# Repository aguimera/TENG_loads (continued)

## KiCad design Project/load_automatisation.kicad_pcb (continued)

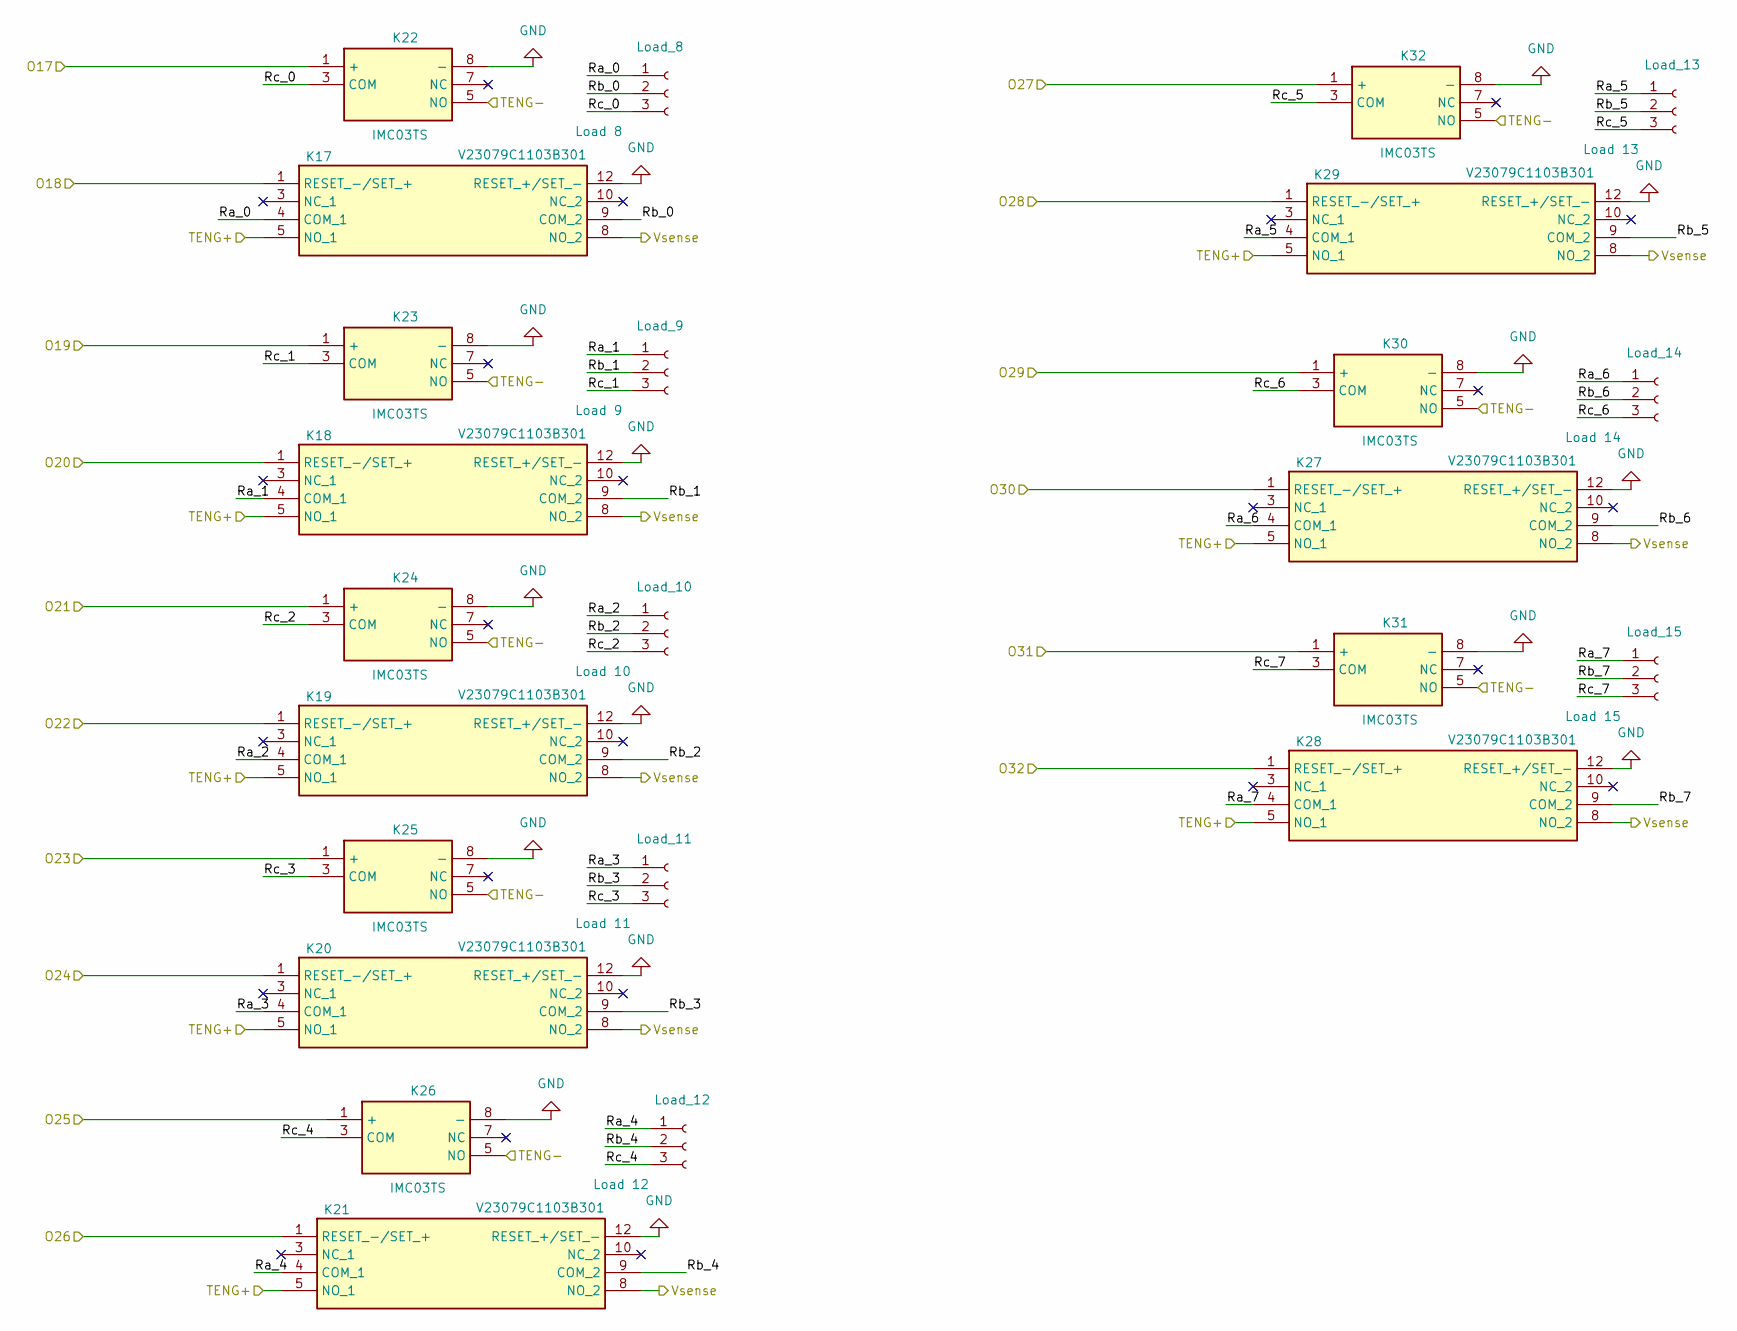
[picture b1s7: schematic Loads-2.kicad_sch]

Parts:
K17, K18, K19, K20, K21, K27, K28, K29: V23079C1103B301; V23079A1001B301; Manufacturer_Part_Number V23079C1103B301; Mouser Part Number 655-V23079C1103B301
K22, K23, K24, K25, K26, K30, K31, K32: IMC03TS; Manufacturer_Part_Number IMC03TS; Mouser Part Number 655-IMC03TS
Load_8: Load 8; PinHeader_1x03_P2.54mm_Vertical
Load_9: Load 9; PinHeader_1x03_P2.54mm_Vertical
Load_10: Load 10; PinHeader_1x03_P2.54mm_Vertical
Load_11: Load 11; PinHeader_1x03_P2.54mm_Vertical
Load_12: Load 12; PinHeader_1x03_P2.54mm_Vertical
Load_13: Load 13; PinHeader_1x03_P2.54mm_Vertical
Load_14: Load 14; PinHeader_1x03_P2.54mm_Vertical
Load_15: Load 15; PinHeader_1x03_P2.54mm_Vertical

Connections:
/2_Loads/Loads-2/Ra_0: K17.4 (COM_1), Load_8.1
/2_Loads/Loads-2/Ra_1: K18.4 (COM_1), Load_9.1
/2_Loads/Loads-2/Ra_2: K19.4 (COM_1), Load_10.1
/2_Loads/Loads-2/Ra_3: K20.4 (COM_1), Load_11.1
/2_Loads/Loads-2/Ra_4: K21.4 (COM_1), Load_12.1
/2_Loads/Loads-2/Ra_5: K29.4 (COM_1), Load_13.1
/2_Loads/Loads-2/Ra_6: K27.4 (COM_1), Load_14.1
/2_Loads/Loads-2/Ra_7: K28.4 (COM_1), Load_15.1
/2_Loads/Loads-2/Rb_0: K17.9 (COM_2), Load_8.2
/2_Loads/Loads-2/Rb_1: K18.9 (COM_2), Load_9.2
/2_Loads/Loads-2/Rb_2: K19.9 (COM_2), Load_10.2
/2_Loads/Loads-2/Rb_3: K20.9 (COM_2), Load_11.2
/2_Loads/Loads-2/Rb_4: K21.9 (COM_2), Load_12.2
/2_Loads/Loads-2/Rb_5: K29.9 (COM_2), Load_13.2
/2_Loads/Loads-2/Rb_6: K27.9 (COM_2), Load_14.2
/2_Loads/Loads-2/Rb_7: K28.9 (COM_2), Load_15.2
/2_Loads/Loads-2/Rc_0: K22.3 (COM), Load_8.3
/2_Loads/Loads-2/Rc_1: K23.3 (COM), Load_9.3
/2_Loads/Loads-2/Rc_2: K24.3 (COM), Load_10.3
/2_Loads/Loads-2/Rc_3: K25.3 (COM), Load_11.3
/2_Loads/Loads-2/Rc_4: K26.3 (COM), Load_12.3
/2_Loads/Loads-2/Rc_5: K32.3 (COM), Load_13.3
/2_Loads/Loads-2/Rc_6: K30.3 (COM), Load_14.3
/2_Loads/Loads-2/Rc_7: K31.3 (COM), Load_15.3
/2_Loads/O17: K22.1 (+); also elsewhere on the board
/2_Loads/O18: K17.1 (RESET_-/SET_+); also elsewhere on the board
/2_Loads/O19: K23.1 (+); also elsewhere on the board
/2_Loads/O20: K18.1 (RESET_-/SET_+); also elsewhere on the board
/2_Loads/O21: K24.1 (+); also elsewhere on the board
/2_Loads/O22: K19.1 (RESET_-/SET_+); also elsewhere on the board
/2_Loads/O23: K25.1 (+); also elsewhere on the board
/2_Loads/O24: K20.1 (RESET_-/SET_+); also elsewhere on the board
/2_Loads/O25: K26.1 (+); also elsewhere on the board
/2_Loads/O26: K21.1 (RESET_-/SET_+); also elsewhere on the board
/2_Loads/O27: K32.1 (+); also elsewhere on the board
/2_Loads/O28: K29.1 (RESET_-/SET_+); also elsewhere on the board
/2_Loads/O29: K30.1 (+); also elsewhere on the board
/2_Loads/O30: K27.1 (RESET_-/SET_+); also elsewhere on the board
/2_Loads/O31: K31.1 (+); also elsewhere on the board
/2_Loads/O32: K28.1 (RESET_-/SET_+); also elsewhere on the board
/Teng+: K17.5 (NO_1), K18.5 (NO_1), K19.5 (NO_1), K20.5 (NO_1), K21.5 (NO_1), K27.5 (NO_1), K28.5 (NO_1), K29.5 (NO_1); also elsewhere on the board
/Teng-: K22.5 (NO), K23.5 (NO), K24.5 (NO), K25.5 (NO), K26.5 (NO), K30.5 (NO), K31.5 (NO), K32.5 (NO); also elsewhere on the board
/Vsense: K17.8 (NO_2), K18.8 (NO_2), K19.8 (NO_2), K20.8 (NO_2), K21.8 (NO_2), K27.8 (NO_2), K28.8 (NO_2), K29.8 (NO_2); also elsewhere on the board
GND: K17.12 (RESET_+/SET_-), K18.12 (RESET_+/SET_-), K19.12 (RESET_+/SET_-), K20.12 (RESET_+/SET_-), K21.12 (RESET_+/SET_-), K22.8 (-), K23.8 (-), K24.8 (-), K25.8 (-), K26.8 (-), K27.12 (RESET_+/SET_-), K28.12 (RESET_+/SET_-), K29.12 (RESET_+/SET_-), K30.8 (-), K31.8 (-), K32.8 (-); also elsewhere on the board

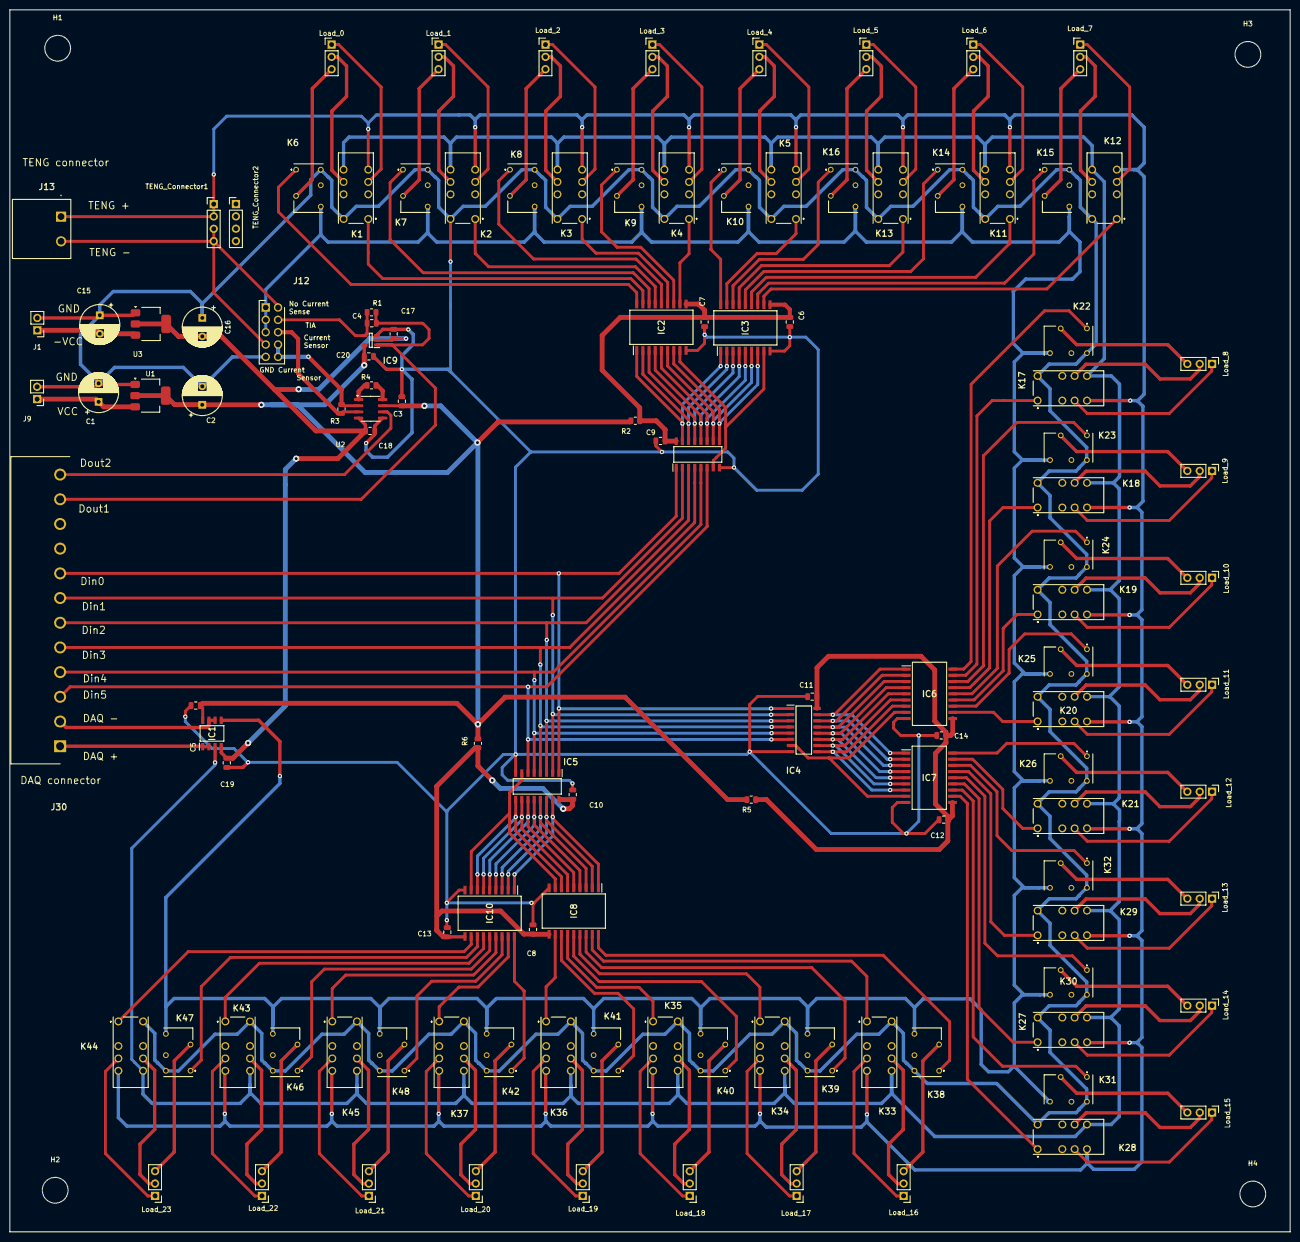
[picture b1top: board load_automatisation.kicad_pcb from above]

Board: 2 copper layers, 263.4 x 251.4 mm, 123 parts (0 on the bottom side), 171 nets.

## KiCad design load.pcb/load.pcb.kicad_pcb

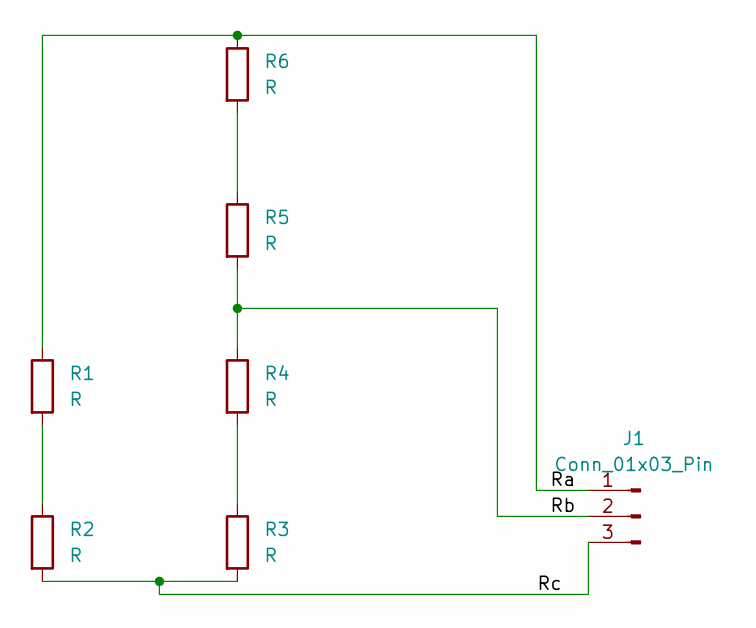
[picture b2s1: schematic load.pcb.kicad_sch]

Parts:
J1: Conn_01x03_Pin; PinHeader_1x03_P2.54mm_Horizontal
R1: R; R_Axial_DIN0614_L14.3mm_D5.7mm_P20.32mm_Horizontal
R2, R3, R4, R5, R6: R; R_0805_2012Metric

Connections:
/Ra: J1.1, R1.1, R6.1
/Rb: J1.2, R4.1, R5.2
/Rc: J1.3, R2.2, R3.2
unnamed: R1.2, R2.1
unnamed: R3.1, R4.2
unnamed: R5.1, R6.2

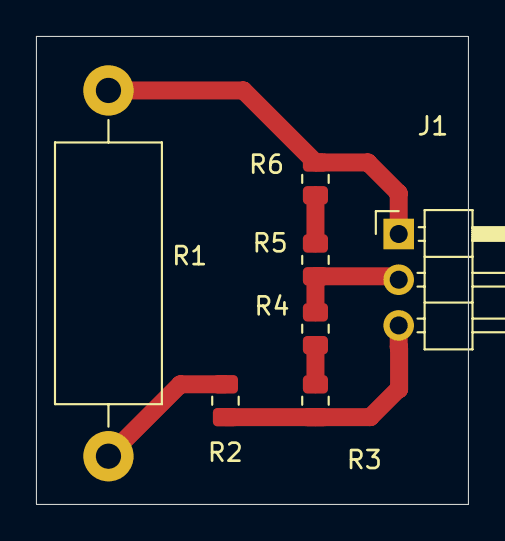
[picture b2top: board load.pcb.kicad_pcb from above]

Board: 2 copper layers, 24.0 x 26.0 mm, 7 parts (0 on the bottom side), 6 nets.

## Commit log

2024-10-15 update gitnore
2024-10-15 new schematic
2024-10-16 update schematic
2024-10-25 new 24 loads 25/10
2024-11-08 new 08/11
2024-11-18 ruoting strategy
2024-11-25 routing 25/11
2024-11-28 routing 28/11
2024-12-03 routing 03/12
2024-12-05 abre alimentacio
2024-12-10 routing 10/12
2024-12-10 place arrangement
2024-12-11 routing 11/12
2024-12-12 new routing 12/12
2025-01-16 new 16/01
